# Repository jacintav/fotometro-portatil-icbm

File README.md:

# Fotómetro portátil (ICBM)

Proyecto de integración de Electrónica Biomédica, Universidad del Desarrollo. Grupo 8.

**Equipo:** Ivette Avila, Isidora Hernández y Jacinta Vallejos.

## Descripción

Prototipo educativo de bajo costo que mide la **transmitancia relativa** de una muestra líquida. Un LED verde ilumina la muestra y un módulo sensor de luz TEMT6000 mide la luz que la atraviesa. El ESP32-C3 calcula la transmitancia como T = I / I₀, donde I₀ es la intensidad medida con el blanco.

El equipo se opera de forma autónoma:
- **SW1 (MEDIR):** inicia la medición de la muestra.
- **SW2 (CALIBRAR):** ejecuta la calibración de blanco.
- **Pantalla OLED 0.96" (I2C):** muestra los resultados y los mensajes de calibración y de error.

Se alimenta por USB-C (5 V). El regulador del módulo ESP32-C3 entrega 3,3 V al sensor y a la pantalla.

> Uso exclusivamente formativo; no es un instrumento para análisis clínico.

## Componentes principales

| Ref. | Componente | Conexión |
|---|---|---|
| J1, J2 | ESP32-C3 SuperMini (montado en zócalos hembra de 9 pines) | — |
| D1 + R1 | LED verde 5 mm + resistencia de 68 Ω | GPIO4 |
| J3 | Módulo sensor de luz TEMT6000 | SIG → GPIO2 (ADC1) |
| J4 | Pantalla OLED 128×64 0.96" (GND, VCC, SCL, SDA) | SDA → GPIO8, SCL → GPIO9 |
| R2, R3 | Pull-up I2C de 4,7 kΩ | SDA, SCL |
| SW1, SW2 | Pulsadores 6×6 mm THT (activos en BAJO) | GPIO5, GPIO6 |
| R4, R5 | Pull-up de los pulsadores de 10 kΩ | GPIO5, GPIO6 |
| C1 | Condensador cerámico de 100 nF (desacoplo de 3,3 V) | 3V3 – GND |

## PCB

- Placa de 70 × 55 mm con 4 agujeros de montaje M3 (3,2 mm).
- Componentes THT; las pistas van en una sola capa (B.Cu) para fabricarla en la ruteadora CNC.
- Plano de tierra en la cara inferior.
- El DRC de KiCad no arroja errores ni conexiones pendientes.

## Estructura del repositorio

```
├── README.md
├── LICENSE
├── docs/
│   ├── datasheets/      Hojas de datos de la OLED y del TEMT6000
│   ├── bitacora.md      Registro de avances del proyecto
│   └── informes/        Informes de la parte I y la parte II
├── electronica/
│   ├── kicad/           Proyecto KiCad (.kicad_pro, .kicad_sch, .kicad_pcb)
│   ├── libraries/       Bibliotecas propias (no se usaron; solo bibliotecas oficiales de KiCad)
│   └── outputs/         PDF del esquemático, Gerber, taladrado, BOM, STEP e imágenes
├── firmware/            Código del ESP32-C3 (en desarrollo)
└── software/            Herramientas complementarias (sin uso por ahora)
```

## Cómo abrir el diseño

1. Instalar [KiCad](https://www.kicad.org/) (versión 9 o superior).
2. Abrir `electronica/kicad/fotometro_portatil_pcb.kicad_pro`.
3. Desde el gestor de proyecto se puede abrir el esquemático y el editor de PCB. Todos los símbolos y footprints son de las bibliotecas oficiales de KiCad, así que no se necesita instalar bibliotecas adicionales.

## Estado del proyecto

- [x] Esquemático
- [x] Layout de PCB y archivos de fabricación
- [ ] Fabricación de la placa
- [ ] Firmware
- [ ] Armado, caja impresa en 3D y validación funcional

## Licencia

Distribuido bajo la licencia MIT. Ver `LICENSE`.

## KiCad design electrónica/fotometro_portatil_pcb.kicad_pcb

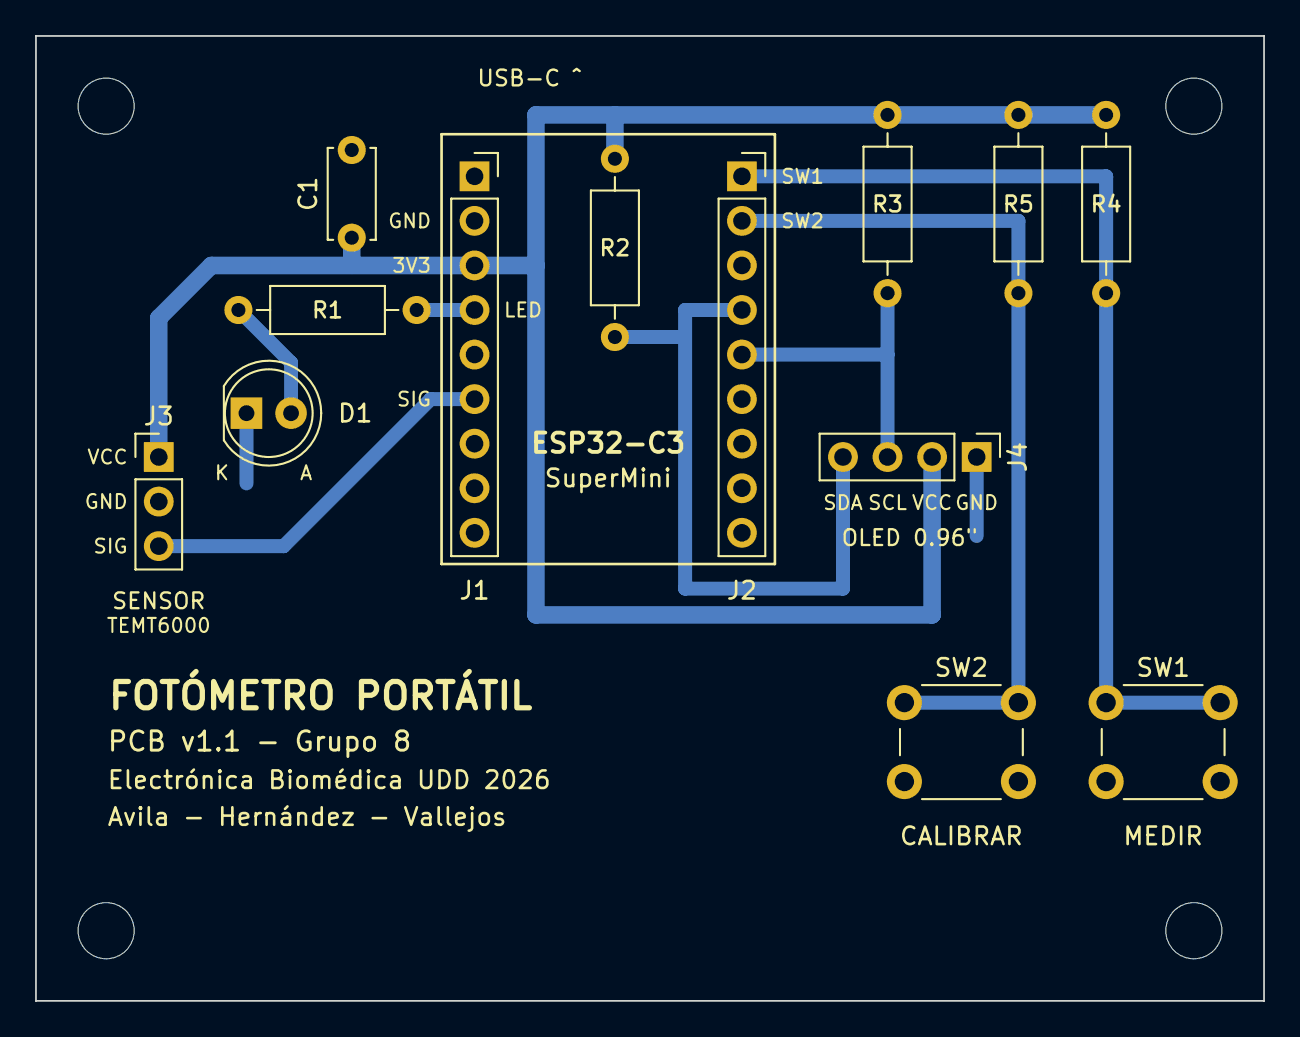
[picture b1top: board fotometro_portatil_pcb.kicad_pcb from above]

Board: 2 copper layers, 70.0 x 55.0 mm, 17 parts (0 on the bottom side), 9 nets.

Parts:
C1: 100nF; C_Disc_D5.0mm_W2.5mm_P5.00mm
D1: LED verde; LED_D5.0mm
H1, H2, H3, H4: MountingHole_3.2mm_M3
J1: ESP32-C3 izq; PinSocket_1x09_P2.54mm_Vertical
J2: ESP32-C3 der; PinSocket_1x09_P2.54mm_Vertical
J3: TEMT6000; PinHeader_1x03_P2.54mm_Vertical
J4: OLED I2C; PinHeader_1x04_P2.54mm_Vertical
R1: 68Ω; R_Axial_DIN0207_L6.3mm_D2.5mm_P10.16mm_Horizontal
R2, R3: 4.7kΩ; R_Axial_DIN0207_L6.3mm_D2.5mm_P10.16mm_Horizontal
R4, R5: 10kΩ; R_Axial_DIN0207_L6.3mm_D2.5mm_P10.16mm_Horizontal
SW1: MEDIR; SW_PUSH_6mm
SW2: CALIBRAR; SW_PUSH_6mm

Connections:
+3V3: C1.1, J1.3, J3.1, J4.2, R2.1, R3.1, R4.2, R5.2
BTN_CALIB: J2.2, R5.1, SW2.1
BTN_MEDIR: J2.1, R4.1, SW1.1
GND: C1.2, D1.1, J1.2, J3.2, J4.1, SW1.2, SW2.2
LED: J1.4, R1.2
unnamed: D1.2, R1.1
SCL: J2.5, J4.3, R3.2
SDA: J2.4, J4.4, R2.2
SIG_SENSOR: J1.6, J3.3
